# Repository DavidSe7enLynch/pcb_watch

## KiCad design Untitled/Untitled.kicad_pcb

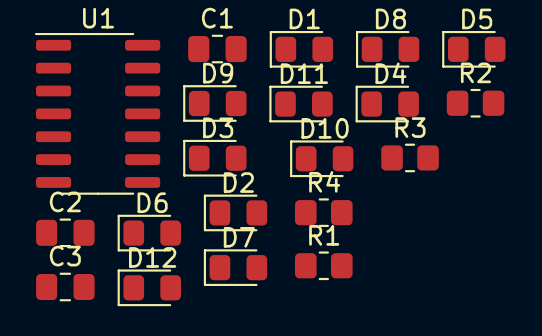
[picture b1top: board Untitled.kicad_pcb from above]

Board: 2 copper layers, 20 parts (0 on the bottom side), 12 nets, no tracks yet.

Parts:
C1, C2, C3: C; C_0805_2012Metric_Pad1.18x1.45mm_HandSolder
D1, D2, D3, D4, D5, D6, D7, D8, D9, D10, D11, D12: LED; LED_0805_2012Metric_Pad1.15x1.40mm_HandSolder
R1, R2, R3, R4: R; R_0805_2012Metric_Pad1.20x1.40mm_HandSolder
U1: ATtiny414-SS; SOIC-14_3.9x8.7mm_P1.27mm

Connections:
GND: C1.1, C2.1, C3.1, U1.14 (GND)
unnamed: C1.2, U1.7 (PB2)
unnamed: C2.2, U1.6 (PB3)
unnamed: R1.1, U1.11 (PA1)
unnamed: R2.1, U1.2 (PA4)
unnamed: R3.1, U1.3 (PA5)
unnamed: R4.1, U1.4 (PA6)
PA1: D4.2 (A), D5.1 (K), D6.2 (A), D7.1 (K), D8.2 (A), D12.1 (K), R1.2
PA4: D3.1 (K), D7.2 (A), D8.1 (K), D9.2 (A), D10.1 (K), D11.2 (A), R2.2
PA5: D1.1 (K), D2.2 (A), D6.1 (K), D10.2 (A), D11.1 (K), D12.2 (A), R3.2
PA6: D1.2 (A), D2.1 (K), D3.2 (A), D4.1 (K), D5.2 (A), D9.1 (K), R4.2
VCC: C3.2, U1.1 (VCC)

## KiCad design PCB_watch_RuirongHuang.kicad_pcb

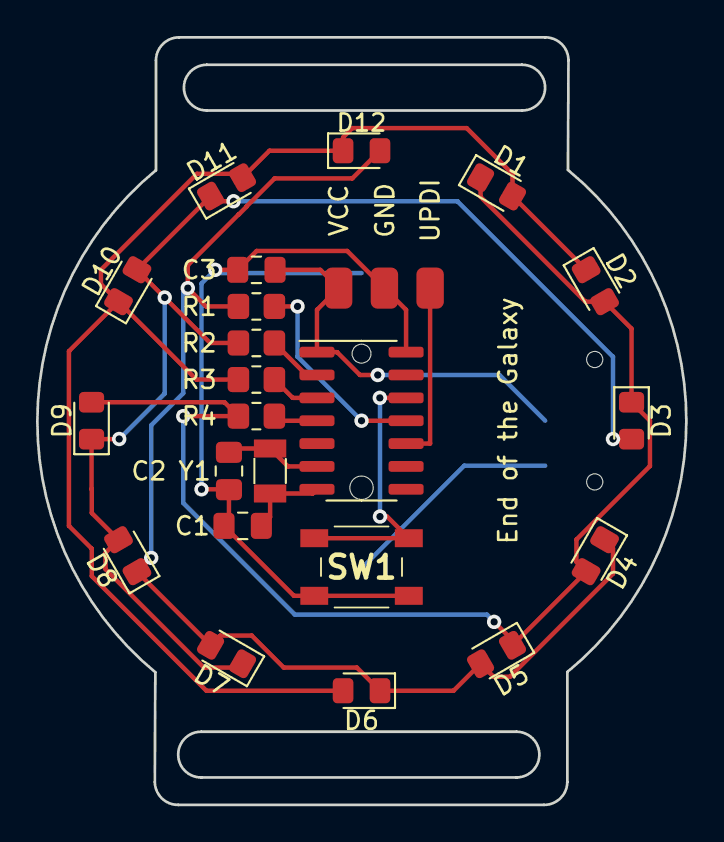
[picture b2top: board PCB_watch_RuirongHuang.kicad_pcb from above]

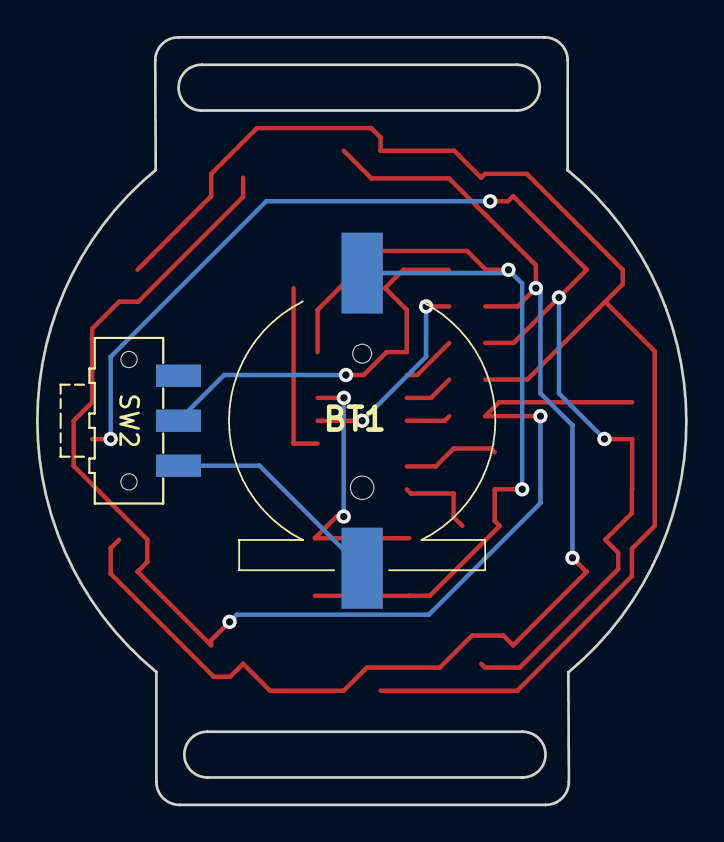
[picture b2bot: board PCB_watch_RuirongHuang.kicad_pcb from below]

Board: 2 copper layers, 36.1 x 42.6 mm, 25 parts (2 on the bottom side), 15 nets.

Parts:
BT1: Battery_Cell; S8411-45R_1
C1, C2, C3: C; C_0805_2012Metric_Pad1.18x1.45mm_HandSolder
D1, D2, D3, D4, D5, D6, D7, D8, D9, D10, D11, D12: LED; LED_0805_2012Metric_Pad1.15x1.40mm_HandSolder
J1: Conn_01x03_Male; UPDI_programmer
R1, R2, R3, R4: R; R_0805_2012Metric_Pad1.20x1.40mm_HandSolder
SW1: SW_MEC_5E; PTS647SN50SMTR2LFS
SW2: SW_SPDT; SW_SPDT_CK-JS102011SAQN
U1: ATtiny414-SS; SOIC-14_3.9x8.7mm_P1.27mm
Y1: Crystal; Crystal_SMD_3215-2Pin_3.2x1.5mm

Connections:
GND: BT1.2 (-), C1.1, C2.1, C3.1, J1.2, SW1.3 (K), SW1.4 (A), U1.14 (GND)
unnamed: BT1.1 (+), SW2.3 (C)
unnamed: C1.2, U1.7 (PB2), Y1.2
unnamed: C2.2, U1.6 (PB3), Y1.1
unnamed: R1.1, U1.11 (PA1)
unnamed: R2.1, U1.2 (PA4)
unnamed: R3.1, U1.3 (PA5)
unnamed: R4.1, U1.4 (PA6)
PA1: D4.1 (K), D5.2 (A), D6.1 (K), D7.2 (A), D8.1 (K), D12.2 (A), R1.2
PA4: D3.2 (A), D7.1 (K), D8.2 (A), D9.1 (K), D10.2 (A), D11.1 (K), R2.2
PA5: D1.2 (A), D2.1 (K), D6.2 (A), D10.1 (K), D11.2 (A), D12.1 (K), R3.2
PA6: D1.1 (K), D2.2 (A), D3.1 (K), D4.2 (A), D5.1 (K), D9.2 (A), R4.2
UPDI: J1.3, U1.10 (~RESET/PA0)
VCC: C3.2, J1.1, SW2.2 (B), U1.1 (VCC)
button: SW1.1, SW1.2, U1.12 (PA2)
